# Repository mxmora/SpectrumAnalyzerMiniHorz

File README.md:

# SpectrumAnalyzerMiniHorz
SpectrumAnalyzerMiniHorz

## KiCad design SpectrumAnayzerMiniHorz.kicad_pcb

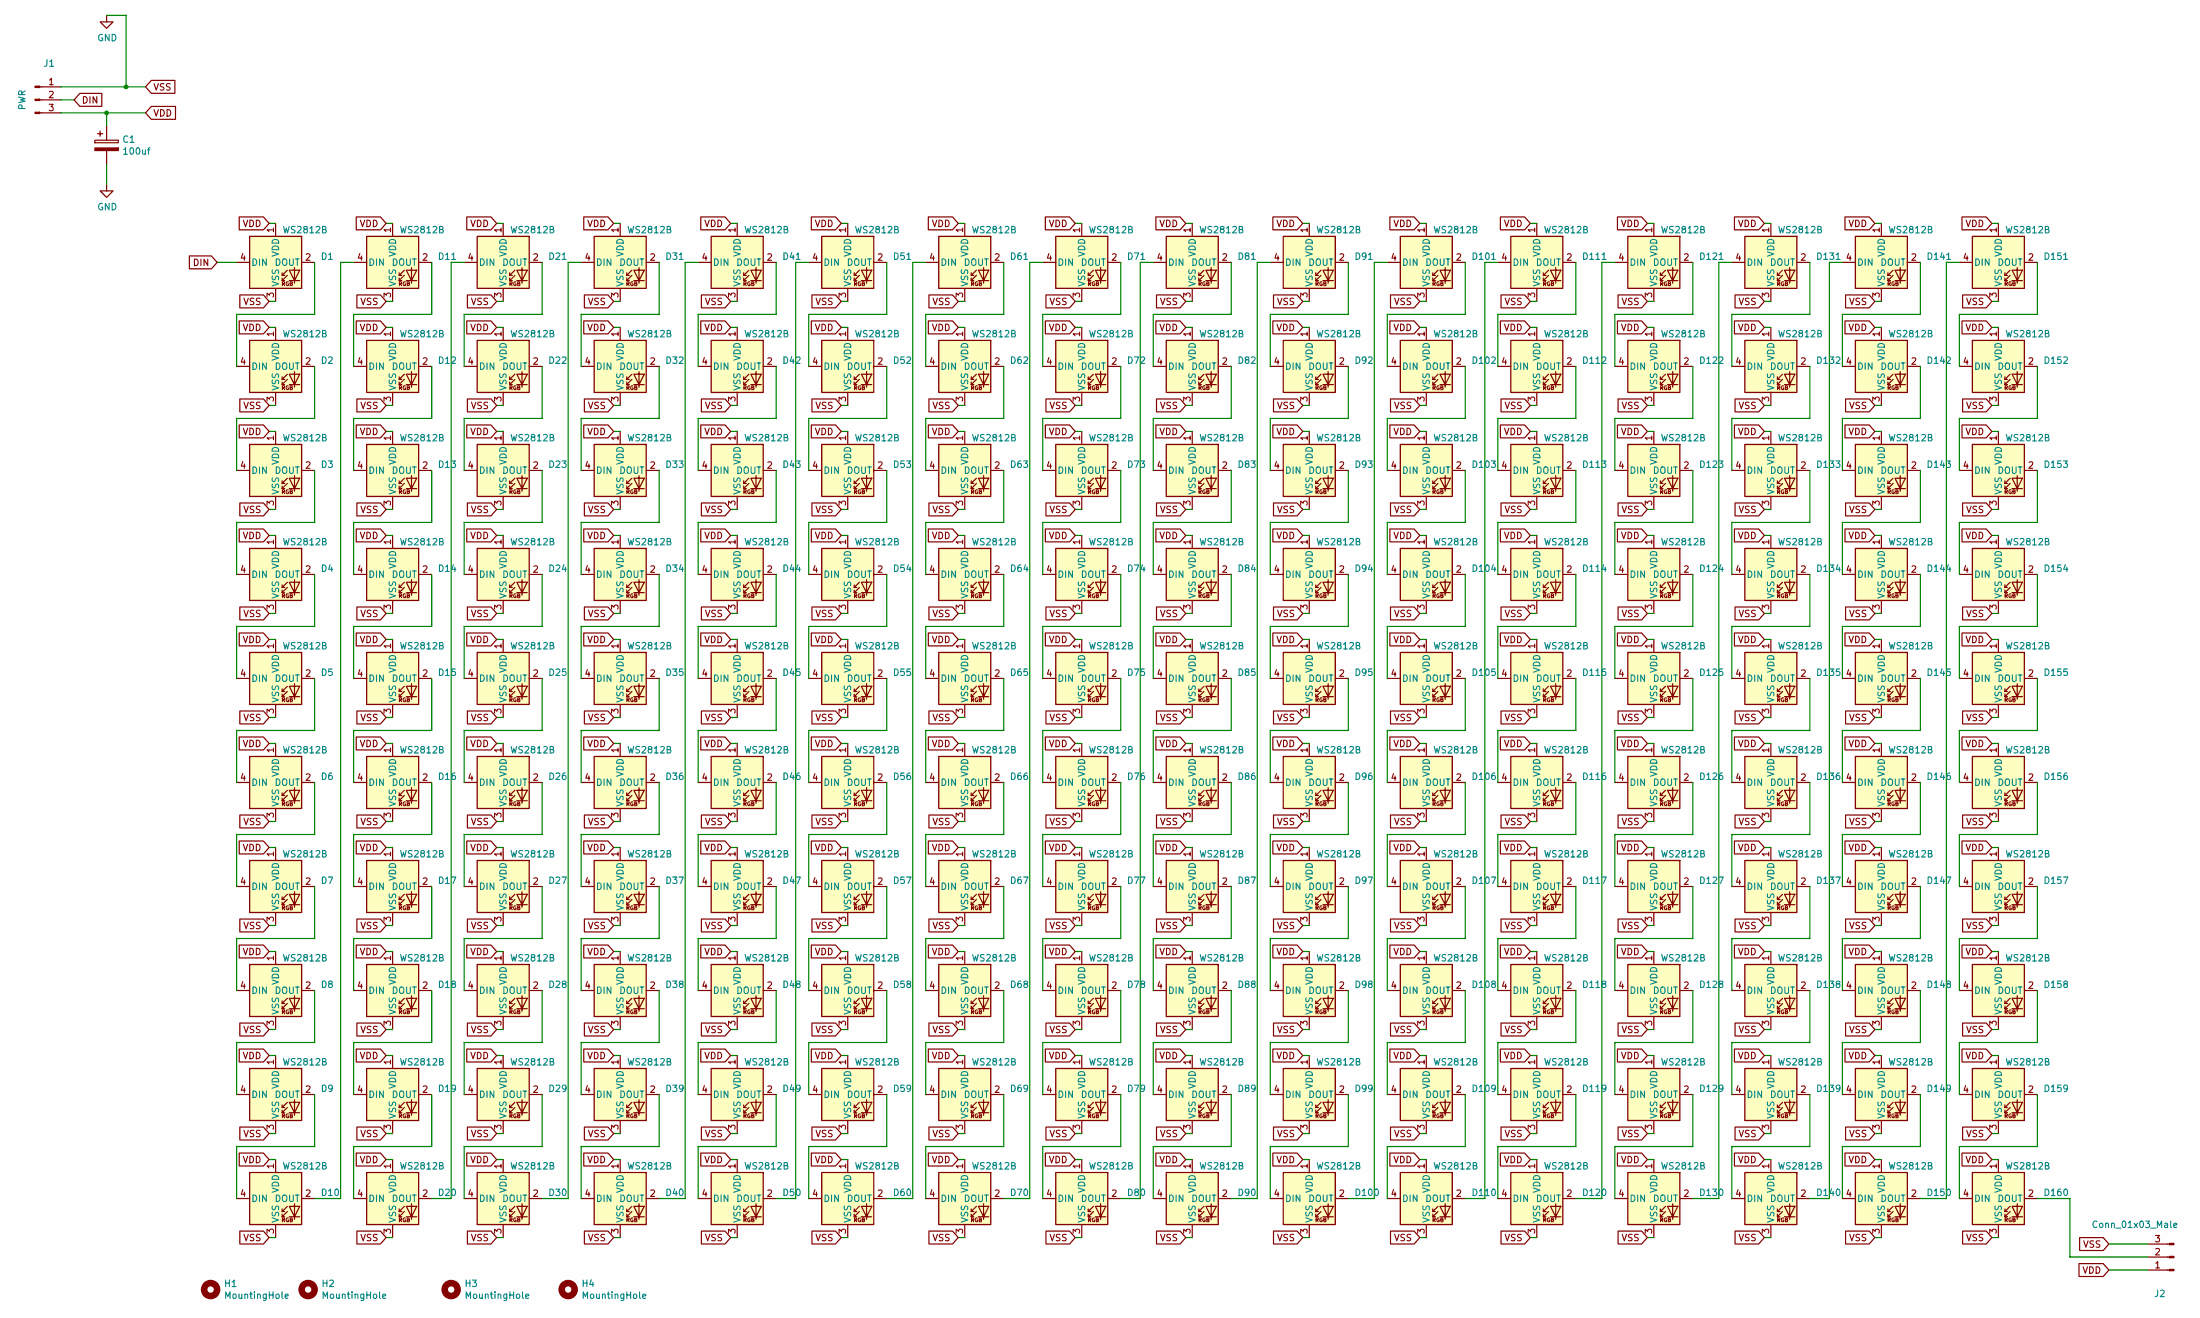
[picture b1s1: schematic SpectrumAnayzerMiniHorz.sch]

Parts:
C1: 100uf; CP_Radial_D5.0mm_P2.50mm
D1: WS2812B; LED_SK6812MINI_PLCC4_3.5x3.5mm_P1.75mm; LCSC C114586
D2, D3, D4, D5, D6, D7, D8, D9, D10, D11, D12, D13, D14, D15, D16, D17, D18, D19, D20, D21, D22, D23, D24, D25, D26, D27, D28, D29, D30, D31, D32, D33, D34, D35, D36, D37, D38, D39, D40, D41, D42, D43, D44, D45, D46, D47, D48, D49, D50, D51, D52, D53, D54, D55, D56, D57, D58, D59, D60, D61, D62, D63, D64, D65, D66, D67, D68, D69, D70, D71, D72, D73, D74, D75, D76, D77, D78, D79, D80, D81, D82, D83, D84, D85, D86, D87, D88, D89, D90, D91, D92, D93, D94, D95, D96, D97, D98, D99, D100, D101, D102, D103, D104, D105, D106, D107, D108, D109, D110, D111, D112, D113, D114, D115, D116, D117, D118, D119, D120, D121, D122, D123, D124, D125, D126, D127, D128, D129, D130, D131, D132, D133, D134, D135, D136, D137, D138, D139, D140, D141, D142, D143, D144, D145, D146, D147, D148, D149, D150, D151, D152, D153, D154, D155, D156, D157, D158, D159, D160: WS2812B; LED_SK6812MINI_PLCC4_3.5x3.5mm_P1.75mm
H1, H2, H3, H4: MountingHole; MountingHole_2.5mm
J1: PWR; PinHeader_1x03_P2.54mm_Vertical
J2: Conn_01x03_Male; PinHeader_1x03_P2.54mm_Vertical

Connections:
DIN: D1.4 (DIN), J1.2
unnamed: D1.2 (DOUT), D2.4 (DIN)
unnamed: D2.2 (DOUT), D3.4 (DIN)
unnamed: D3.2 (DOUT), D4.4 (DIN)
unnamed: D4.2 (DOUT), D5.4 (DIN)
unnamed: D5.2 (DOUT), D6.4 (DIN)
unnamed: D6.2 (DOUT), D7.4 (DIN)
unnamed: D7.2 (DOUT), D8.4 (DIN)
unnamed: D8.2 (DOUT), D9.4 (DIN)
unnamed: D10.2 (DOUT), D11.4 (DIN)
unnamed: D9.2 (DOUT), D10.4 (DIN)
unnamed: D11.2 (DOUT), D12.4 (DIN)
unnamed: D12.2 (DOUT), D13.4 (DIN)
unnamed: D13.2 (DOUT), D14.4 (DIN)
unnamed: D14.2 (DOUT), D15.4 (DIN)
unnamed: D15.2 (DOUT), D16.4 (DIN)
unnamed: D16.2 (DOUT), D17.4 (DIN)
unnamed: D17.2 (DOUT), D18.4 (DIN)
unnamed: D18.2 (DOUT), D19.4 (DIN)
unnamed: D19.2 (DOUT), D20.4 (DIN)
unnamed: D20.2 (DOUT), D21.4 (DIN)
unnamed: D21.2 (DOUT), D22.4 (DIN)
unnamed: D22.2 (DOUT), D23.4 (DIN)
unnamed: D23.2 (DOUT), D24.4 (DIN)
unnamed: D24.2 (DOUT), D25.4 (DIN)
unnamed: D25.2 (DOUT), D26.4 (DIN)
unnamed: D26.2 (DOUT), D27.4 (DIN)
unnamed: D27.2 (DOUT), D28.4 (DIN)
unnamed: D28.2 (DOUT), D29.4 (DIN)
unnamed: D29.2 (DOUT), D30.4 (DIN)
unnamed: D30.2 (DOUT), D31.4 (DIN)
unnamed: D31.2 (DOUT), D32.4 (DIN)
unnamed: D32.2 (DOUT), D33.4 (DIN)
unnamed: D33.2 (DOUT), D34.4 (DIN)
unnamed: D34.2 (DOUT), D35.4 (DIN)
unnamed: D35.2 (DOUT), D36.4 (DIN)
unnamed: D36.2 (DOUT), D37.4 (DIN)
unnamed: D37.2 (DOUT), D38.4 (DIN)
unnamed: D38.2 (DOUT), D39.4 (DIN)
unnamed: D39.2 (DOUT), D40.4 (DIN)
unnamed: D40.2 (DOUT), D41.4 (DIN)
unnamed: D41.2 (DOUT), D42.4 (DIN)
unnamed: D42.2 (DOUT), D43.4 (DIN)
unnamed: D43.2 (DOUT), D44.4 (DIN)
unnamed: D44.2 (DOUT), D45.4 (DIN)
unnamed: D45.2 (DOUT), D46.4 (DIN)
unnamed: D46.2 (DOUT), D47.4 (DIN)
unnamed: D47.2 (DOUT), D48.4 (DIN)
unnamed: D48.2 (DOUT), D49.4 (DIN)
unnamed: D49.2 (DOUT), D50.4 (DIN)
unnamed: D50.2 (DOUT), D51.4 (DIN)
unnamed: D51.2 (DOUT), D52.4 (DIN)
unnamed: D52.2 (DOUT), D53.4 (DIN)
unnamed: D53.2 (DOUT), D54.4 (DIN)
unnamed: D54.2 (DOUT), D55.4 (DIN)
unnamed: D55.2 (DOUT), D56.4 (DIN)
unnamed: D56.2 (DOUT), D57.4 (DIN)
unnamed: D57.2 (DOUT), D58.4 (DIN)
unnamed: D58.2 (DOUT), D59.4 (DIN)
unnamed: D59.2 (DOUT), D60.4 (DIN)
unnamed: D60.2 (DOUT), D61.4 (DIN)
unnamed: D61.2 (DOUT), D62.4 (DIN)
unnamed: D62.2 (DOUT), D63.4 (DIN)
unnamed: D63.2 (DOUT), D64.4 (DIN)
unnamed: D64.2 (DOUT), D65.4 (DIN)
unnamed: D65.2 (DOUT), D66.4 (DIN)
unnamed: D66.2 (DOUT), D67.4 (DIN)
unnamed: D67.2 (DOUT), D68.4 (DIN)
unnamed: D68.2 (DOUT), D69.4 (DIN)
unnamed: D69.2 (DOUT), D70.4 (DIN)
unnamed: D70.2 (DOUT), D71.4 (DIN)
unnamed: D71.2 (DOUT), D72.4 (DIN)
unnamed: D72.2 (DOUT), D73.4 (DIN)
unnamed: D73.2 (DOUT), D74.4 (DIN)
unnamed: D74.2 (DOUT), D75.4 (DIN)
unnamed: D75.2 (DOUT), D76.4 (DIN)
unnamed: D76.2 (DOUT), D77.4 (DIN)
unnamed: D77.2 (DOUT), D78.4 (DIN)
unnamed: D78.2 (DOUT), D79.4 (DIN)
unnamed: D79.2 (DOUT), D80.4 (DIN)
unnamed: D80.2 (DOUT), D81.4 (DIN)
unnamed: D81.2 (DOUT), D82.4 (DIN)
unnamed: D82.2 (DOUT), D83.4 (DIN)
unnamed: D83.2 (DOUT), D84.4 (DIN)
unnamed: D84.2 (DOUT), D85.4 (DIN)
unnamed: D85.2 (DOUT), D86.4 (DIN)
unnamed: D86.2 (DOUT), D87.4 (DIN)
unnamed: D87.2 (DOUT), D88.4 (DIN)
unnamed: D88.2 (DOUT), D89.4 (DIN)
unnamed: D89.2 (DOUT), D90.4 (DIN)
unnamed: D90.2 (DOUT), D91.4 (DIN)
unnamed: D91.2 (DOUT), D92.4 (DIN)
unnamed: D92.2 (DOUT), D93.4 (DIN)
unnamed: D93.2 (DOUT), D94.4 (DIN)
unnamed: D94.2 (DOUT), D95.4 (DIN)
unnamed: D95.2 (DOUT), D96.4 (DIN)
unnamed: D96.2 (DOUT), D97.4 (DIN)
unnamed: D97.2 (DOUT), D98.4 (DIN)
unnamed: D98.2 (DOUT), D99.4 (DIN)
unnamed: D100.2 (DOUT), D101.4 (DIN)
unnamed: D99.2 (DOUT), D100.4 (DIN)
unnamed: D101.2 (DOUT), D102.4 (DIN)
unnamed: D102.2 (DOUT), D103.4 (DIN)
unnamed: D103.2 (DOUT), D104.4 (DIN)
unnamed: D104.2 (DOUT), D105.4 (DIN)
unnamed: D105.2 (DOUT), D106.4 (DIN)
unnamed: D106.2 (DOUT), D107.4 (DIN)
unnamed: D107.2 (DOUT), D108.4 (DIN)
unnamed: D108.2 (DOUT), D109.4 (DIN)
unnamed: D109.2 (DOUT), D110.4 (DIN)
unnamed: D110.2 (DOUT), D111.4 (DIN)
unnamed: D111.2 (DOUT), D112.4 (DIN)
unnamed: D112.2 (DOUT), D113.4 (DIN)
unnamed: D113.2 (DOUT), D114.4 (DIN)
unnamed: D114.2 (DOUT), D115.4 (DIN)
unnamed: D115.2 (DOUT), D116.4 (DIN)
unnamed: D116.2 (DOUT), D117.4 (DIN)
unnamed: D117.2 (DOUT), D118.4 (DIN)
unnamed: D118.2 (DOUT), D119.4 (DIN)
unnamed: D119.2 (DOUT), D120.4 (DIN)
unnamed: D120.2 (DOUT), D121.4 (DIN)
unnamed: D121.2 (DOUT), D122.4 (DIN)
unnamed: D122.2 (DOUT), D123.4 (DIN)
unnamed: D123.2 (DOUT), D124.4 (DIN)
unnamed: D124.2 (DOUT), D125.4 (DIN)
unnamed: D125.2 (DOUT), D126.4 (DIN)
unnamed: D126.2 (DOUT), D127.4 (DIN)
unnamed: D127.2 (DOUT), D128.4 (DIN)
unnamed: D128.2 (DOUT), D129.4 (DIN)
unnamed: D129.2 (DOUT), D130.4 (DIN)
unnamed: D130.2 (DOUT), D131.4 (DIN)
unnamed: D131.2 (DOUT), D132.4 (DIN)
unnamed: D132.2 (DOUT), D133.4 (DIN)
unnamed: D133.2 (DOUT), D134.4 (DIN)
unnamed: D134.2 (DOUT), D135.4 (DIN)
unnamed: D135.2 (DOUT), D136.4 (DIN)
unnamed: D136.2 (DOUT), D137.4 (DIN)
unnamed: D137.2 (DOUT), D138.4 (DIN)
unnamed: D138.2 (DOUT), D139.4 (DIN)
unnamed: D139.2 (DOUT), D140.4 (DIN)
unnamed: D140.2 (DOUT), D141.4 (DIN)
unnamed: D141.2 (DOUT), D142.4 (DIN)
unnamed: D142.2 (DOUT), D143.4 (DIN)
unnamed: D143.2 (DOUT), D144.4 (DIN)
unnamed: D144.2 (DOUT), D145.4 (DIN)
unnamed: D145.2 (DOUT), D146.4 (DIN)
unnamed: D146.2 (DOUT), D147.4 (DIN)
unnamed: D147.2 (DOUT), D148.4 (DIN)
unnamed: D148.2 (DOUT), D149.4 (DIN)
unnamed: D149.2 (DOUT), D150.4 (DIN)
unnamed: D150.2 (DOUT), D151.4 (DIN)
unnamed: D151.2 (DOUT), D152.4 (DIN)
unnamed: D152.2 (DOUT), D153.4 (DIN)
unnamed: D153.2 (DOUT), D154.4 (DIN)
unnamed: D154.2 (DOUT), D155.4 (DIN)
unnamed: D155.2 (DOUT), D156.4 (DIN)
unnamed: D156.2 (DOUT), D157.4 (DIN)
unnamed: D157.2 (DOUT), D158.4 (DIN)
unnamed: D158.2 (DOUT), D159.4 (DIN)
unnamed: D159.2 (DOUT), D160.4 (DIN)
unnamed: D160.2 (DOUT), J2.2
VDD: C1.1, D1.1 (VDD), D2.1 (VDD), D3.1 (VDD), D4.1 (VDD), D5.1 (VDD), D6.1 (VDD), D7.1 (VDD), D8.1 (VDD), D9.1 (VDD), D10.1 (VDD), D11.1 (VDD), D12.1 (VDD), D13.1 (VDD), D14.1 (VDD), D15.1 (VDD), D16.1 (VDD), D17.1 (VDD), D18.1 (VDD), D19.1 (VDD), D20.1 (VDD), D21.1 (VDD), D22.1 (VDD), D23.1 (VDD), D24.1 (VDD), D25.1 (VDD), D26.1 (VDD), D27.1 (VDD), D28.1 (VDD), D29.1 (VDD), D30.1 (VDD), D31.1 (VDD), D32.1 (VDD), D33.1 (VDD), D34.1 (VDD), D35.1 (VDD), D36.1 (VDD), D37.1 (VDD), D38.1 (VDD), D39.1 (VDD), D40.1 (VDD), D41.1 (VDD), D42.1 (VDD), D43.1 (VDD), D44.1 (VDD), D45.1 (VDD), D46.1 (VDD), D47.1 (VDD), D48.1 (VDD), D49.1 (VDD), D50.1 (VDD), D51.1 (VDD), D52.1 (VDD), D53.1 (VDD), D54.1 (VDD), D55.1 (VDD), D56.1 (VDD), D57.1 (VDD), D58.1 (VDD), D59.1 (VDD), D60.1 (VDD), D61.1 (VDD), D62.1 (VDD), D63.1 (VDD), D64.1 (VDD), D65.1 (VDD), D66.1 (VDD), D67.1 (VDD), D68.1 (VDD), D69.1 (VDD), D70.1 (VDD), D71.1 (VDD), D72.1 (VDD), D73.1 (VDD), D74.1 (VDD), D75.1 (VDD), D76.1 (VDD), D77.1 (VDD), D78.1 (VDD), D79.1 (VDD), D80.1 (VDD), D81.1 (VDD), D82.1 (VDD), D83.1 (VDD), D84.1 (VDD), D85.1 (VDD), D86.1 (VDD), D87.1 (VDD), D88.1 (VDD), D89.1 (VDD), D90.1 (VDD), D91.1 (VDD), D92.1 (VDD), D93.1 (VDD), D94.1 (VDD), D95.1 (VDD), D96.1 (VDD), D97.1 (VDD), D98.1 (VDD), D99.1 (VDD), D100.1 (VDD), D101.1 (VDD), D102.1 (VDD), D103.1 (VDD), D104.1 (VDD), D105.1 (VDD), D106.1 (VDD), D107.1 (VDD), D108.1 (VDD), D109.1 (VDD), D110.1 (VDD), D111.1 (VDD), D112.1 (VDD), D113.1 (VDD), D114.1 (VDD), D115.1 (VDD), D116.1 (VDD), D117.1 (VDD), D118.1 (VDD), D119.1 (VDD), D120.1 (VDD), D121.1 (VDD), D122.1 (VDD), D123.1 (VDD), D124.1 (VDD), D125.1 (VDD), D126.1 (VDD), D127.1 (VDD), D128.1 (VDD), D129.1 (VDD), D130.1 (VDD), D131.1 (VDD), D132.1 (VDD), D133.1 (VDD), D134.1 (VDD), D135.1 (VDD), D136.1 (VDD), D137.1 (VDD), D138.1 (VDD), D139.1 (VDD), D140.1 (VDD), D141.1 (VDD), D142.1 (VDD), D143.1 (VDD), D144.1 (VDD), D145.1 (VDD), D146.1 (VDD), D147.1 (VDD), D148.1 (VDD), D149.1 (VDD), D150.1 (VDD), D151.1 (VDD), D152.1 (VDD), D153.1 (VDD), D154.1 (VDD), D155.1 (VDD), D156.1 (VDD), D157.1 (VDD), D158.1 (VDD), D159.1 (VDD), D160.1 (VDD), J1.3, J2.1
VSS: C1.2, D1.3 (VSS), D2.3 (VSS), D3.3 (VSS), D4.3 (VSS), D5.3 (VSS), D6.3 (VSS), D7.3 (VSS), D8.3 (VSS), D9.3 (VSS), D10.3 (VSS), D11.3 (VSS), D12.3 (VSS), D13.3 (VSS), D14.3 (VSS), D15.3 (VSS), D16.3 (VSS), D17.3 (VSS), D18.3 (VSS), D19.3 (VSS), D20.3 (VSS), D21.3 (VSS), D22.3 (VSS), D23.3 (VSS), D24.3 (VSS), D25.3 (VSS), D26.3 (VSS), D27.3 (VSS), D28.3 (VSS), D29.3 (VSS), D30.3 (VSS), D31.3 (VSS), D32.3 (VSS), D33.3 (VSS), D34.3 (VSS), D35.3 (VSS), D36.3 (VSS), D37.3 (VSS), D38.3 (VSS), D39.3 (VSS), D40.3 (VSS), D41.3 (VSS), D42.3 (VSS), D43.3 (VSS), D44.3 (VSS), D45.3 (VSS), D46.3 (VSS), D47.3 (VSS), D48.3 (VSS), D49.3 (VSS), D50.3 (VSS), D51.3 (VSS), D52.3 (VSS), D53.3 (VSS), D54.3 (VSS), D55.3 (VSS), D56.3 (VSS), D57.3 (VSS), D58.3 (VSS), D59.3 (VSS), D60.3 (VSS), D61.3 (VSS), D62.3 (VSS), D63.3 (VSS), D64.3 (VSS), D65.3 (VSS), D66.3 (VSS), D67.3 (VSS), D68.3 (VSS), D69.3 (VSS), D70.3 (VSS), D71.3 (VSS), D72.3 (VSS), D73.3 (VSS), D74.3 (VSS), D75.3 (VSS), D76.3 (VSS), D77.3 (VSS), D78.3 (VSS), D79.3 (VSS), D80.3 (VSS), D81.3 (VSS), D82.3 (VSS), D83.3 (VSS), D84.3 (VSS), D85.3 (VSS), D86.3 (VSS), D87.3 (VSS), D88.3 (VSS), D89.3 (VSS), D90.3 (VSS), D91.3 (VSS), D92.3 (VSS), D93.3 (VSS), D94.3 (VSS), D95.3 (VSS), D96.3 (VSS), D97.3 (VSS), D98.3 (VSS), D99.3 (VSS), D100.3 (VSS), D101.3 (VSS), D102.3 (VSS), D103.3 (VSS), D104.3 (VSS), D105.3 (VSS), D106.3 (VSS), D107.3 (VSS), D108.3 (VSS), D109.3 (VSS), D110.3 (VSS), D111.3 (VSS), D112.3 (VSS), D113.3 (VSS), D114.3 (VSS), D115.3 (VSS), D116.3 (VSS), D117.3 (VSS), D118.3 (VSS), D119.3 (VSS), D120.3 (VSS), D121.3 (VSS), D122.3 (VSS), D123.3 (VSS), D124.3 (VSS), D125.3 (VSS), D126.3 (VSS), D127.3 (VSS), D128.3 (VSS), D129.3 (VSS), D130.3 (VSS), D131.3 (VSS), D132.3 (VSS), D133.3 (VSS), D134.3 (VSS), D135.3 (VSS), D136.3 (VSS), D137.3 (VSS), D138.3 (VSS), D139.3 (VSS), D140.3 (VSS), D141.3 (VSS), D142.3 (VSS), D143.3 (VSS), D144.3 (VSS), D145.3 (VSS), D146.3 (VSS), D147.3 (VSS), D148.3 (VSS), D149.3 (VSS), D150.3 (VSS), D151.3 (VSS), D152.3 (VSS), D153.3 (VSS), D154.3 (VSS), D155.3 (VSS), D156.3 (VSS), D157.3 (VSS), D158.3 (VSS), D159.3 (VSS), D160.3 (VSS), J1.1, J2.3

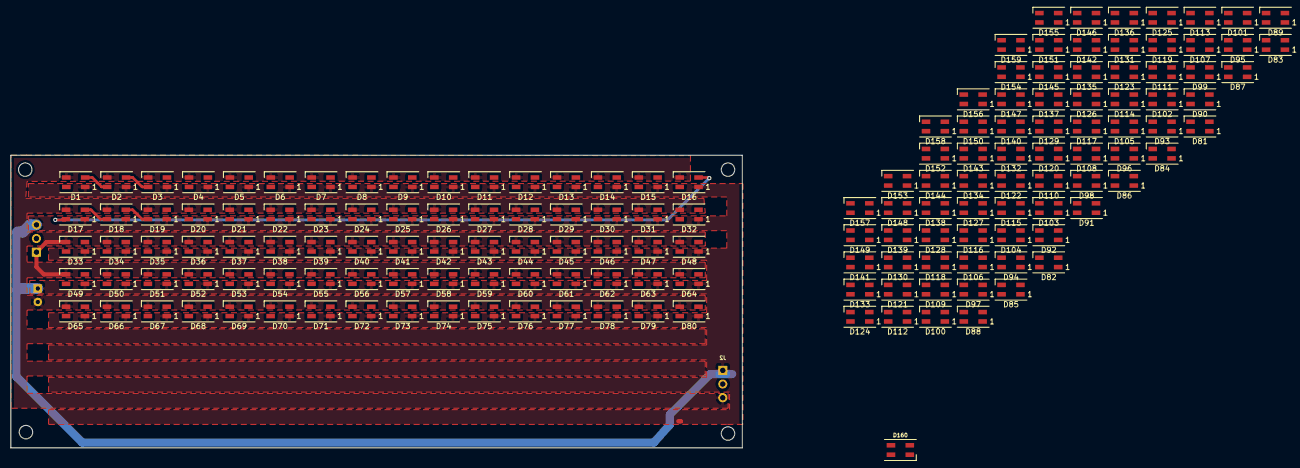
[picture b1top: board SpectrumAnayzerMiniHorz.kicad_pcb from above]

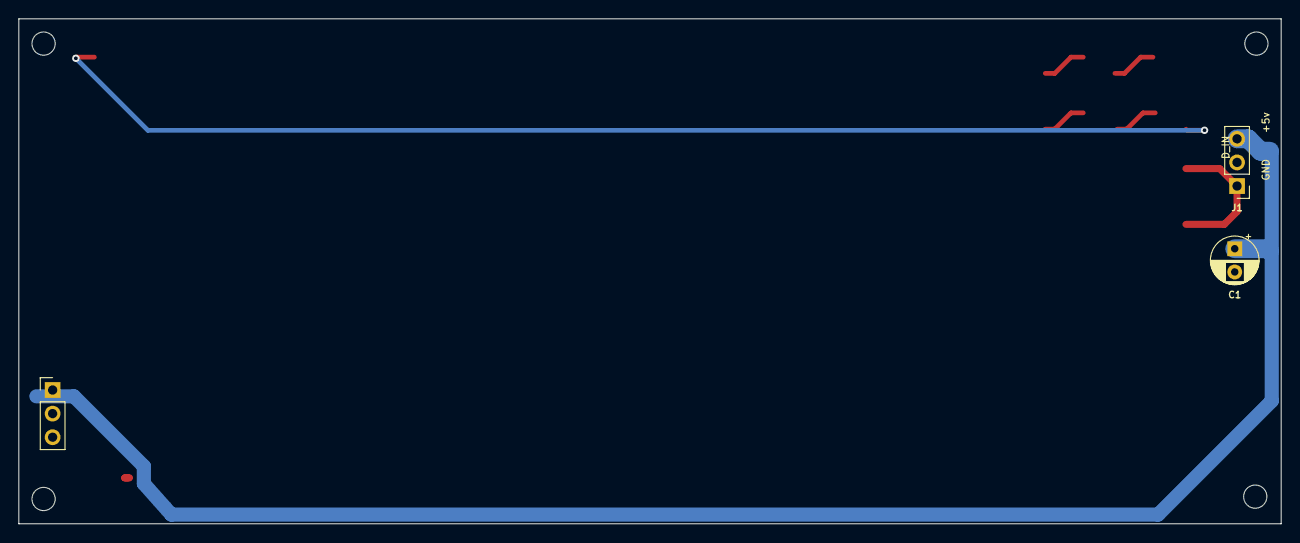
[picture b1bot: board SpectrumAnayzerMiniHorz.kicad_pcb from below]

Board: 2 copper layers, 135.9 x 54.4 mm, 167 parts (3 on the bottom side), 163 nets.

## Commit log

2020-03-03 first check in
